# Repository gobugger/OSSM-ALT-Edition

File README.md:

# OSSM ALT Edition
---
## 🎯 Overview

OSSM ALT Edition is a community-driven alternative version of the well-known [OSSM](https://github.com/KinkyMakers/OSSM-hardware) platform. A lot of time and effort has gone into this project. This has been possible thanks to all the previous work that has been done and several community members that helped test this. Do note that we are still in 'beta testing' phase and that you may run into issues. Please provide feedback to help improve the project. This project represents a ground-up redesign focused on:

- **Modern Power Delivery**: Custom 28V 140W USB-C PCB with comprehensive protection circuits
- **Simplified Assembly**: All-in-one clean design with easily sourceable components
- **European Sourcing**: BOM optimized for availability in Europe
- **Enhanced Performance**: Support for MGN12H and MGN15H rails with support for belts up to 15mm belt.
- **Open Source**: Fully open hardware

***Links***: KM [Discord community](https://kinkymakers.com) & [Ko-Fi](https://ko-fi.com/dododesigns) (for contributions / buying boards)

<sub>**Notice**: This version was developed without any involvement of the original OSSM / Research and Desire members. However, none of this would have been possible without their prior work which is greatly appreciated. Especially the work of [ArmpitMFG](https://github.com/armpitMFG) has been a great inspiration. </sub>

---

## ✨ Key Features

### Hardware Improvements
- **Custom 28V USB-C PCB** with extensive protection circuits
  - Over/under voltage protection
  - Reverse current protection
  - ESD protection on all exposed ports
  - Inrush current limiting
  - Hybrid polymer capacitors for stable power
  - Brake Chopper Add-On 360Watt
- **Dual Rail Options**
  - MGN15H for heavy-duty applications (up to 15mm belts)
  - MGN12H for lighter builds (up to 12mm belts)
- **Efficient Travel**: Rail length minus 150mm usable stroke
- **Compatible with Pitclamp Mini** and includes optimized alternative design with dowels

### Electronics & Firmware
- **ESP32-S3** microcontroller with integrated RS485 controller
- **WS2812 Status LED** (firmware support pending)
- **Made for [OSSM Rust](https://github.com/orange-gem/ossm-rs)** firmware
- Compatible with step/dir control for original firmware adaptation
- **Optional Brake Chopper PCB** for enhanced safety

### Design Philosophy
- Optimized for 3D printing (minimal supports required)
- Common, easily sourceable components
- Clean, simple assembly
- Comprehensive protection systems

---
  
## 📦 Bill of Materials

A comprehensive BOM with descriptions and links can be found [here](Assembly-Info/BOM-OSSM-ALT.csv). However, the parts below are a quick summary everything you need for building this complete version:

| **Part**           | **Description**                                             | **Costs** |
| -------------- | -------------------------------------------------------- | ----- |
| 57AIM30        | Motor                                                    | €110  |
| MGN15H Rail    | Rail 40cm                                                | €25   |
| Or MGN12H Rail    | Rail 40cm                                                | €21   |
| 625RS Bearing  | Belt Bearings                                            | €15   |
| M5 Bolts       | Complete kit                                             | €12   |
| M3 Bolts       | Complete kit                                             | €12   |
| Dowel Pins     | Precision pins                                           | €10    |
| GT2 Belt       | 50cm                                                     | €15   |
| GT2 20T pulley | 15mm                                                     | €10    | 
| Filament  | Max 500g | €20   |
| OSSM ALT 28V PCB   | Designs available for self-sourcing or buy through me to support this project. | €40   |
| **Total**      | Rough approximation. Check BOM for details.              | €270  |

📋 **[Complete BOM with part numbers and links](Assembly-Info/BOM-OSSM-ALT.csv)**

> **Note**: You will also need a remote control device. Compatible options include:
> - Official R&D remote
> - iOS/Android apps
> - Web control interface
> - M5 Remote (check firmware compatibility)

---

## 3D Printing Tips

500 grams of filament should be enough to complete the whole build including the main pitclamp (350 without). It is optimized as much as possible for 3D printing with only 1 part requiring a small amount of supports. The filament type should not matter for most standard build, but heavy users might want to rely on something sturdier like tough-PLA, PET-G, ASA or PC. The test builds have been printed with standard Bambulab basic PLA (Not matte/silk). 

**Filament Required**: ~500g for complete build including Pitclamp

**Recommended Materials**:
- **Standard Use**: PLA, PLA+
- **Heavy Use**: Tough-PLA, PETG, ASA, PC

**Important**: Follow the [detailed 3D printing guide](Assembly-Info/Print-Manual/README.md) carefully to ensure proper fit and function.

**Print Options**:
- Standard version (no branding)
- Multi-color branded version (AMS/toolchanger compatible)
- Single-color embossed version

---
## Assembly:

📺 **Video Assembly Guides**:
- [Part 1](https://youtu.be/EqzNXQzpHu0) 
- [Part 2](https://youtu.be/FnY4Sz64H2A) 

📖 **Written Assembly Guide**: In development

💬 **Need Help?** Join the KM [Discord community](https://kinkymakers.com) for assembly support and questions (Look for the OSSM ALT Project).

---

## 🔌 Main PCB Specifications

Most work has gone into this PCB. My vision for this Machine/PCB is that groups of people will self-source this PCB. From 10+ pieces this makes sense, so as long as you can find 10 people you should be able to buy this at an affordable price. The rest of the machine can be printed and uses off the shelf parts. I will also sell these boards for people that only need 1 PCB and want to help support this project (please not that a lot of my own money has gone into this and any support is greatly appreciated ([Ko-Fi](https://ko-fi.com/dododesigns))

### Technical Features

- **Power**: CH224Q for 28V USB-C PD 3.2 negotiation
- - Continuous 140Watt capable with 4 layer optimized PCB design (load tested)
- **Controller**: ESP32-S3 microcontroller with onboard antenna
- **Communication**: Integrated RS485 controller
- **Power Protection**:
  - Hybrid polymer capacitors
  - Inrush current limiting
  - Over/under voltage protection
  - Reverse current protection
- **Additional Features**:
  - Dedicated USB-C debugging port
  - ESD protection on all exposed ports
  - WS2812 status LED
  - Brake chopper expansion support

**Design Tool**: KiCAD 9  
**Manufacturing**: Optimized for major PCB fabrication houses

### Optional Brake Chopper Add-on

Enhanced protection for heavy-duty use:
- **Dissipation**: 12W continuous, 360W short-term spikes
- **Protection Threshold**: 33V (protects 36V TVS diode)
- **Purpose**: Back-EMF spike suppression
- **Recommended For**: Heavy users and added safety margin

This was mainly a fun side project for me which also adds functionality. It is basically an improved version of a Pololu Shunt Regulator, but completely redesigned with an on-board gate driver, 12V LDO, and 12watts of power resistors (2 sides assembly up to 24watt). This PCB was designed to be very cheap and easy to produce. 

---
## 🔋 Compatible Power Sources

This design is focused around PD, so it only makes sense to provide some options that are tested.

> **Important**: Use a USB-C cable with E-marker chip for >3A current. Standard cables will limit performance.

### Tested & Confirmed

| Device | Type | Rating | Status | Recommended | Rating | Notes |
|--------|------|--------|--------|-------|------|-----|
| [Apple 140W USB-C Adapter](https://www.apple.com/nl/shop/product/mw2m3zm/a/usb%E2%80%91c-lichtnetadapter-van-140-w) | Wall Adapter | 28V / 5A (140W) | 🔬 Tested | ✅ Recommended| ★★★★★ (5)| Excellent reliability and quality, Only ~€60 (will likely not work with other pcb's besides the OSSM ALT since it requires inrush current protection) |
| [Ugreen 200W Powerbank](https://eu.ugreen.com/products/ugreen-nexode-power-bank-200w-25000mah) | Powerbank | 28V / 5A (140W) | 🔬 Tested| ✅ Recommended|★★★★★ (5)| Great portable option that negotiates with almost any chip. Best power bank I have tested.|
| [Anker 140W Wall Adapter](https://www.anker.com/products/a2697-anker-charger-140w-4-port) | Wall Adapter | 28V / 5A (140W) | 🔬 Tested| ✅ Recommended|★★★★☆ (4)| Works well, but you will definitely feel it get hot at prolonged 140W and after 20 minutes or so it will lower the power to cool down. 100Watts continuous is fine so for the gold motor there are no problems. I have yet to see a supported motor that pulls 140W continuous. 
| [Sitecom 140W Wall adapter](https://www.action.com/nl-nl/p/3221194/sitecom-usb-wandoplader/) | Wall Adapter | 28V / 5A (140W)|🔬 Tested | ✅ Recommended| ★★★★☆ (4) | Cheapest adapter of the list (~€20). Did not do any extensive testing yet, but it negotiates 28V and 20V fine. I was also able to load test it at 140W and you can feel it get warmer similar to the Anker one, but it seems to hold up fine. At it's price point it is probably a very good deal (even comes with a cable), but we don't know if it's easy to source since right now it's sold at 'action' which normally changes its inventory quite quickly. 
| [Ugreen 100W Wall Adapter](https://www.amazon.nl/dp/B091TV6LWN) | Wall Adapter | 20V / 5A (100W) | 🔬 Tested | ⚠️ Lower Power|★★★☆☆ (3) |Works okay, but do notice that this one does not support 28V. If you have the OSSM-Alt pcb at 28V and still try to power it, it will work but negotiates down to 20V. |
| [Framework 180W Adapter](https://frame.work/nl/en/products/16-power-adapter?v=FRANCR000F) | Wall Adapter | 36V / 5A (180W) | 🔬 Tested | ⚠️ Lower Power | ★★★☆☆ (3) | Quality wise I believe this is a good adapter, but it has a lot of difficulty negotiating with several common cheap PD chips. So it won't negotiate above 20V on the OSSM-ALT PCB and it also does not seem to support I2C with this chip either. Therefore, not really recommended unless you already have it and just power a motor at max 100W. 
| Apple 67W Adapter | Powerbank | 20V / 3.3A (67W) | 🔬 Tested | ⚠️ Lower Power | ★★☆☆☆ (2.5) | Negotiates well and also supports I2C negotiation. 67W is however on the lower side, so this is definitely not recommended for heavy usage. Still, this was the adapter I first tested my OSSM with and from my experience 67W is enough for most light play.  |
| Xiaomi Mi 50W | Powerbank | 20V / 2A (40W) | 🔬 Tested | ⚠️ Low Power | ★★☆☆☆ (2) | Not recommended. Negotiates well, but low power. Still for a very light weight OSSM it might. be fine.  |

**Have you tested another power source?** Please share your results!

---

## ❤️ Support the Project

If you've built an OSSM ALT and want to support continued development:

### Financial Support

- **PCB Purchase**: Buy boards from me to support the project (Discord PM, Ko-Fi (soon))
- **Buy a hardware kit**: If there is enough demand, I might start selling some hardware kits 
- **Donations**: [Ko-Fi](https://ko-fi.com/dododesigns) *(or contact me on Discord)*

### Non-Financial Support

- ⭐ **Star this repository** to increase visibility
- 📢 **Share the project** with your community
- 📸 **Share your build** with photos and feedback on Discord
- 📖 **Contribute documentation** and improvements

---

## 📜 License

This project is **Open Source Hardware**.

All hardware design files (including PCB schematics, layouts, and 3D mechanical design files) are licensed under the **CERN Open Hardware Licence Version 2 – Strongly Reciprocal (CERN-OHL-S-2.0)**.

You are free to:
- Use, study, modify, and manufacture this design

Under the following conditions:
- **Attribution** must be given to the original author(s)
- **All modified versions and derivatives must be released under the same license**
- **Complete corresponding source files must be made available**

---

## 🙏 Acknowledgments

Special thanks to:

### Core Contributors
- **OrangeMurker & Nakata** - OSSM Rust firmware development and invaluable feedback
- **Beta Testers** - All community members who tested and provided feedback

### Inspiration & Prior Art
- **[armpitMFG](https://github.com/armpitMFG)** - Front/end effector designs and Pitclamp Mini
- **Original OSSM / R&D Team** - Foundation and inspiration for this project

### Community
- All contributors who have improved this design
- Discord community members providing support and feedback

---

## ⚠️ Disclaimer

This project is currently in **beta testing phase**. While extensively tested, you may encounter issues. Please provide feedback to help improve the project.

**Safety**: This is a DIY project involving motors and electronics. Build and use at your own risk. Ensure all safety precautions are followed during assembly and operation.

---

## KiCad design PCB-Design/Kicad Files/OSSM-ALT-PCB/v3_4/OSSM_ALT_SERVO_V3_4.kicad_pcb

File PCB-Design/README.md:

# PCB Design

This folder contains everything related to the two PCBs of the OSSM ALT Edition (the main PCB and the brake chopper), organized as follows:

| Folder | Contents |
| ------ | -------- |
| [Schematic and Design](Schematic%20and%20Design/) | The schematics of both PCBs and their STEP files |
| [Production Files](Production%20Files/) | A manual on ordering, plus all the files needed to produce the PCBs yourself (Gerbers, BOM, CPL) |
| [Kicad Files](Kicad%20Files/) | The KiCad project files, if you wish to edit things |

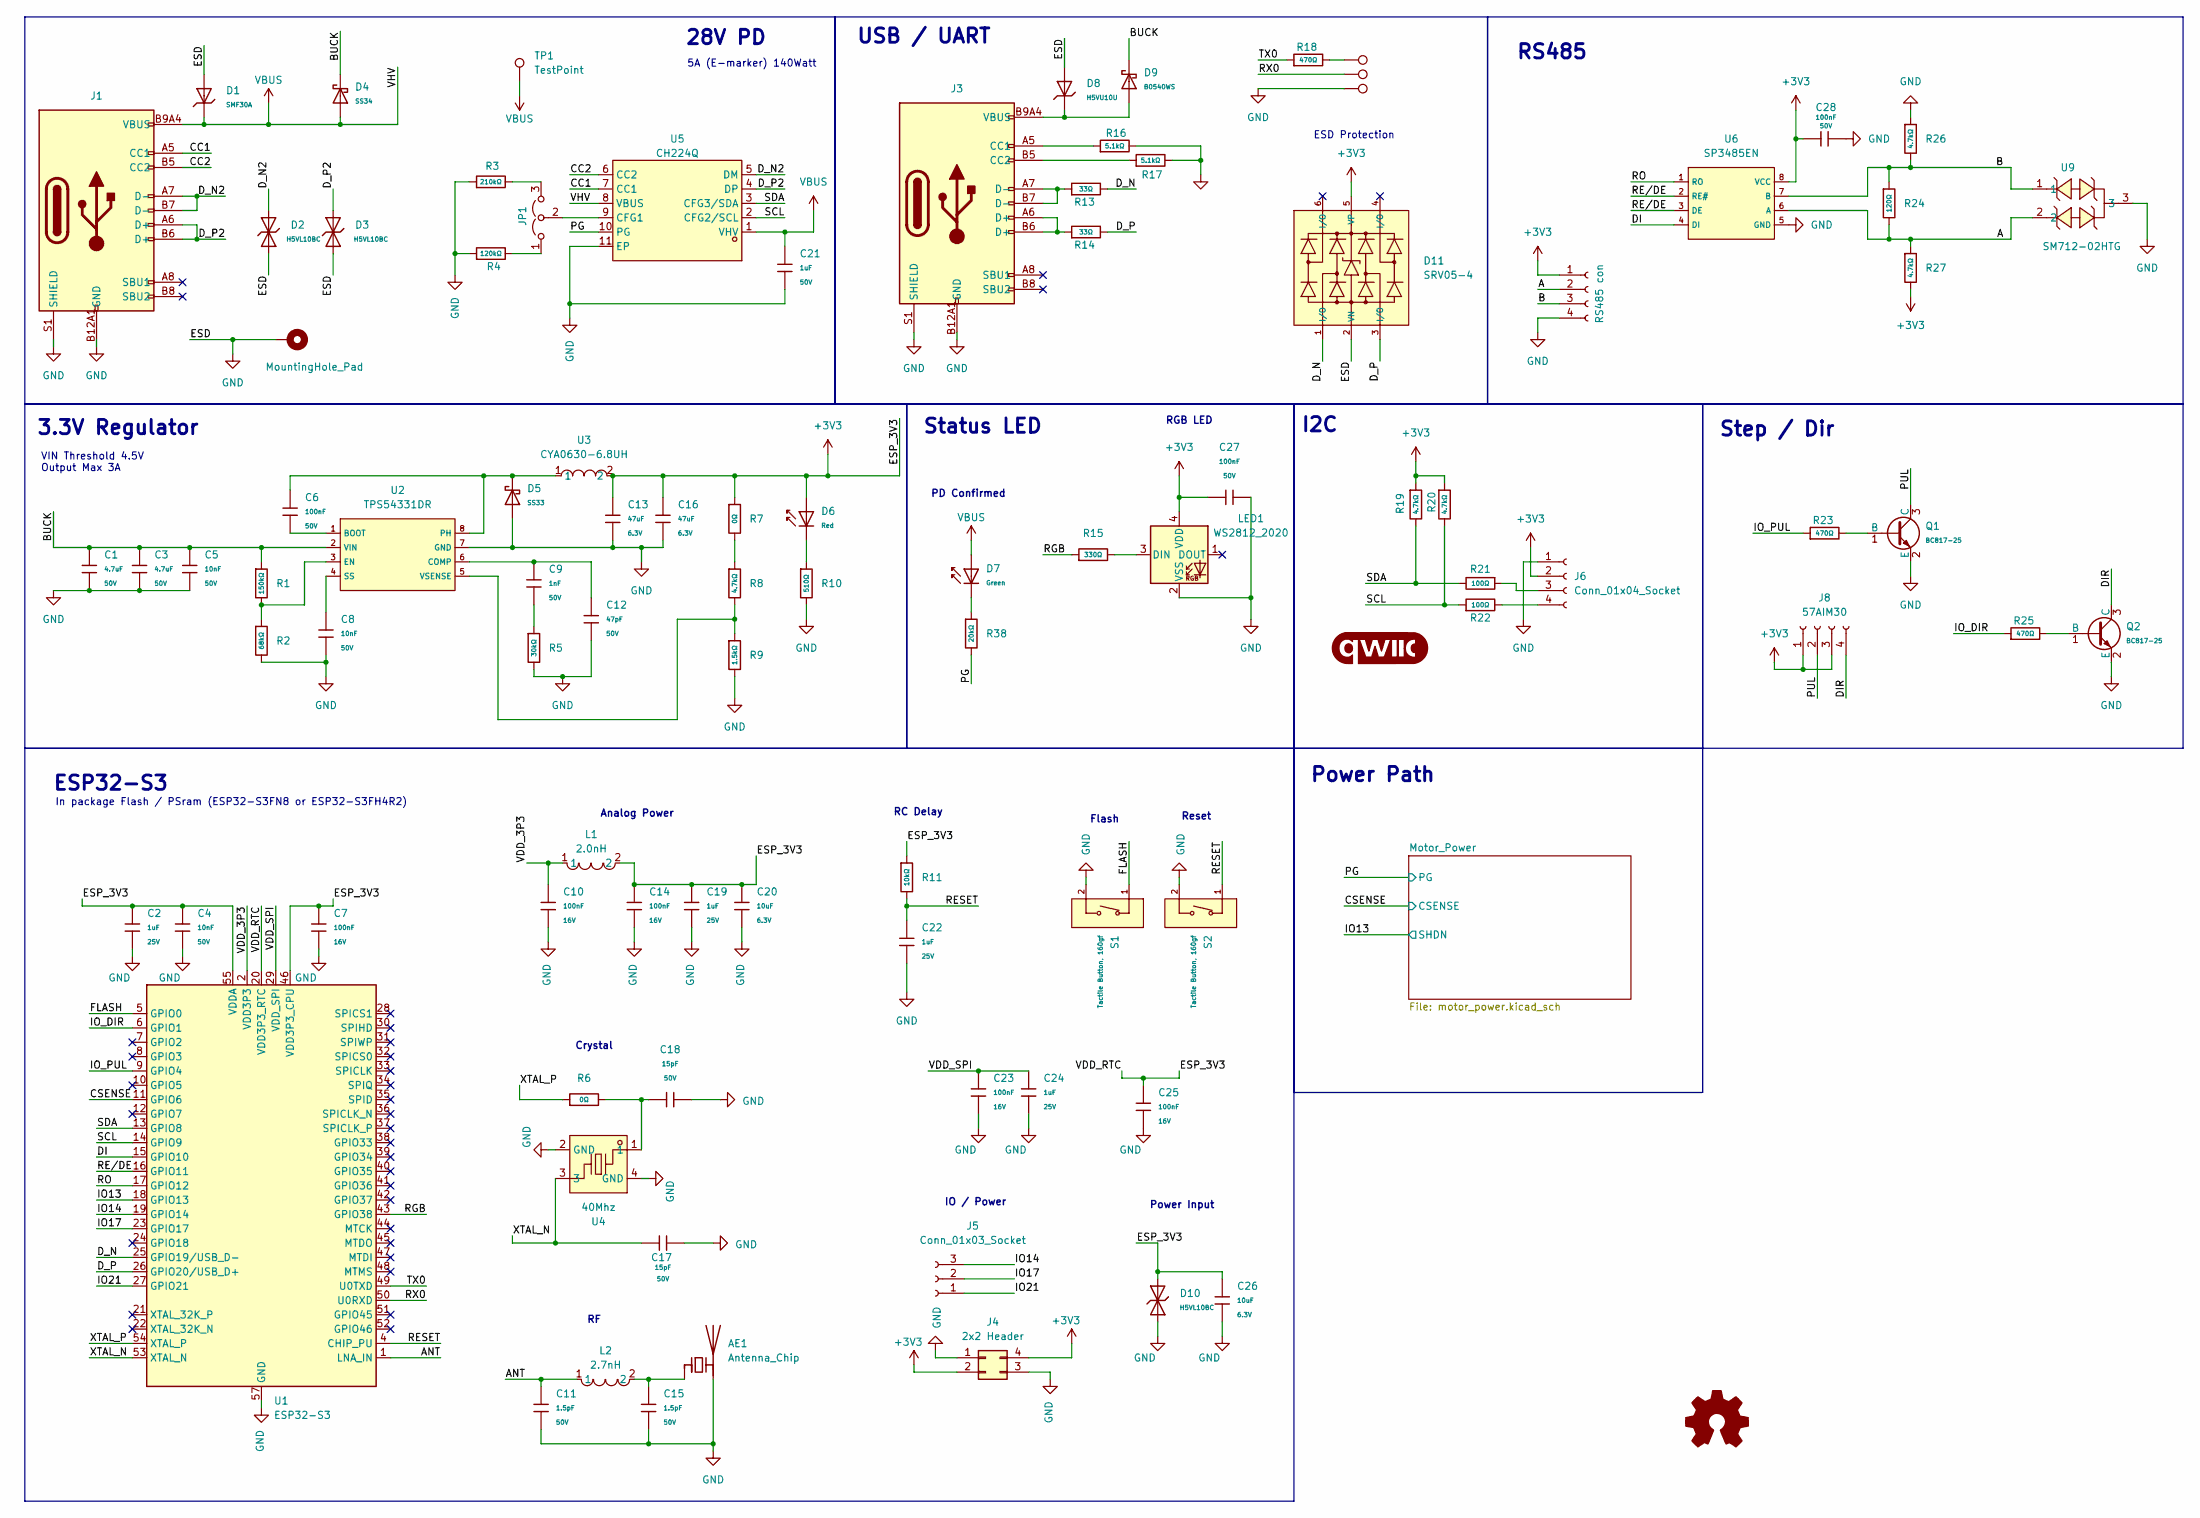
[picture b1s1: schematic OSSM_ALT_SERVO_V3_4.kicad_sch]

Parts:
AE1: Antenna_Chip; Texas_SWRA117D_2.4GHz_Left
C1, C3: 4.7uF; C_1206; Voltage Rated 50V; Tolerance ±10%; Part 1206B475K500NT; LCSC C29823
C2, C19, C22, C24: 1uF; C_0402; Voltage Rated 25V; Tolerance ±10%; Part CL05A105KA5NQNC; LCSC C52923
C4, C5, C8: 10nF; C_0402; Voltage Rated 50V; Tolerance ±10%; Part CL05B103KB5NNNC; LCSC C15195
C6, C27, C28: 100nF; C_0402; Voltage Rated 50V; Tolerance ±10%; Part CL05B104KB54PNC; LCSC C307331
C7, C10, C14, C23, C25: 100nF; C_0402; Voltage Rated 16V; Tolerance ±10%; Part CL05B104KO5NNNC; LCSC C1525
C9: 1nF; C_0402; Voltage Rated 50V; Tolerance ±10%; Part 0402B102K500NT; LCSC C1523
C11, C15: 1.5pF; C_0402; Voltage Rated 50V; Part 0402CG1R5C500NT; LCSC C1552
C12: 47pF; C_0402; Voltage Rated 50V; Tolerance ±5%; Part 0402CG470J500NT; LCSC C1567
C13, C16: 47uF; C_0805; Voltage Rated 6.3V; Tolerance ±20%; Part CL21A476MQYNNNE; LCSC C16780
C17, C18: 15pF; C_0402; Voltage Rated 50V; Tolerance ±5%; Part 0402CG150J500NT; LCSC C1548
C20, C26: 10uF; C_0402; Voltage Rated 6.3V; Tolerance ±20%; Part CL05A106MQ5NUNC; LCSC C15525
C21: 1uF; C_0603; Voltage Rated 50V; Tolerance ±10%; Part CL10A105KB8NNNC; LCSC C15849
D1: SMF30A; D_SOD-123FL; Breakdown Voltage 33.3V; Part SMF30A; LCSC C19077518
D2, D3, D10: H5VL10BC; D_DFN1006-2L; Part H5VL10BC; LCSC C20615784
D4: SS34; D_SMA; Forward Voltage (Vf@If) 550mV@3A; Reverse Voltage (Vr) 40V; Part SS34; LCSC C8678
D5: SS33; D_SMA; Part SS33; LCSC C28646294
D6: Red; D_0603; Part KT-0603R; LCSC C2286
D7: Green; D_0805; Part KT-0805G; LCSC C2297
D8: H5VU10U; D_DFN1006-2L; Breakdown Voltage 9V; Part H5VU10U; LCSC C22395519
D9: B0540WS; D_SOD-323; Part B0540WS; LCSC C7420326
D11: SRV05-4; SOT-23-6_L2.9-W1.6-P0.95-LS2.8-BL-1; Breakdown Voltage (Vbr) 6V; Clamping Voltage@Ipp 12.5V; Part SRV05-4; LCSC C7420376
G1: qwiic_Logo; qwiic_3mm
H1: MountingHole_Pad; MountingHole_3.2mm_M3_Pad
J1, J3: Connector, USB-TYPE-C-16P; TYPE-C-SMD_HX-TYPE-C-16PIN; LCSC C2927039
J4: 2x2 Header; PinHeader_2x02_P2.54mm_Vertical
J5: Conn_01x03_Socket; PinHeader_1x03_P2.54mm_Vertical
J6: Conn_01x04_Socket; JST_SH_SM04B-SRSS-TB_1x04-1MP_P1.00mm_Horizontal; LCSC C51940130
J7: RS485 con; OSSM ALT RS485 Connector
J8: 57AIM30; JST_PH_B4B-PH-K_1x04_P2.00mm_Vertical
JP1: Jumper_3_Open; PinHeader_1x03_P2.54mm_Vertical
L1: 2.0nH; L0402; LCSC Part C18216
L2: 2.7nH; L0402; LCSC C778766
LED1: WS2812_2020; LED_WS2812_2020; LCSC C42417600
Q1, Q2: BC817-25; Q_SOT-23; Part BC817-25; LCSC C20069154
R1: 150kΩ; R_0402; Overload Voltage (Max) 75V; Tolerance ±1%; Part 0603WAF1503T5E; LCSC C25755
R2: 68kΩ; R_0402; Overload Voltage (Max) 75V; Tolerance ±1%; Part 0603WAF6802T5E; LCSC C36871
R3: 210kΩ; R_0603; Overload Voltage (Max) 75V; Tolerance ±1%; Part 0603WAF2203T5E; LCSC C22952
R4: 120kΩ; R_0603; Overload Voltage (Max) 75V; Tolerance ±1%; Part 0603WAF1203T5E; LCSC C25808
R5: 30kΩ; R_0402; Overload Voltage (Max) 75V; Tolerance ±1%; Part 0603WAF3002T5E; LCSC C25553
R6, R7: 0Ω; R_0402; Overload Voltage (Max) 50V; Tolerance ±1%; Part 0402WGF0000TCE; LCSC C17168
R8, R19, R20, R26, R27: 4.7kΩ; R_0402; Overload Voltage (Max) 50V; Tolerance ±1%; Part 0402WGF4701TCE; LCSC C25900
R9: 1.5kΩ; R_0402; Overload Voltage (Max) 50V; Tolerance ±1%; Part 0402WGF1501TCE; LCSC C25867
R10: 510Ω; R_0603; Overload Voltage (Max) 75V; Tolerance ±1%; Part 0603WAF5100T5E; LCSC C23193
R11: 10kΩ; R_0402; Overload Voltage (Max) 50V; Tolerance ±1%; Part 0402WGF1002TCE; LCSC C25744
R13, R14: 33Ω; R_0402; Overload Voltage (Max) 50V; Tolerance ±1%; Part 0402WGF330JTCE; LCSC C25105
R15: 330Ω; R_0402; Overload Voltage (Max) 50V; Tolerance ±1%; Part 0402WGF3300TCE; LCSC C25104
R16, R17: 5.1kΩ; R_0402; Overload Voltage (Max) 50V; Tolerance ±1%; Part 0402WGF5101TCE; LCSC C25905
R18, R23, R25: 470Ω; R_0402; Overload Voltage (Max) 50V; Tolerance ±1%; Part 0402WGF4700TCE; LCSC C25117
R21, R22: 100Ω; R_0402; Overload Voltage (Max) 50V; Tolerance ±1%; Part 0402WGF1000TCE; LCSC C25076
R24: 120Ω; R_0603; Overload Voltage (Max) 75V; Tolerance ±1%; Part 0603WAF1200T5E; LCSC C22787
R38: 20kΩ; R_0603; Overload Voltage (Max) 75V; Tolerance ±1%; Part 0603WAF2002T5E; LCSC C4184
S1, S2: Tactile Button, 160gf; SW_TS-1088-AR02016; Voltage Rating (Dc) 12V; Part TS-1088-AR02016; LCSC C720477
TP1: TestPoint; TestPoint_Pad_D1.0mm
TP2, TP3, TP4: TestPoint; TestPoint_Pad_D1.5mm
U1: ESP32-S3; QFN-56-1EP_7x7mm_P0.4mm_EP4x4mm_ThermalVias; LCSC C2913196
U2: TPS54331DR; SOIC-8_L5.0-W4.0-P1.27-LS6.0-BL; Output Voltage 0.8V~25V; Input Voltage 3.5V~28V; Part TPS54331DR; LCSC C9865
U3: CYA0630-6.8UH; IND-SMD_L7.2-W6.6_GPSR0730; LCSC Part C5189749
U4: 40Mhz; ESP32 40Mhz Crystal C7206306; LCSC Part C7206306
U5: CH224Q; SON-10_L2.0-W2.0-P0.40-TL-EP; LCSC Part C46061833
U6: SP3485EN; SOIC-8_L5.0-W4.0-P1.27-LS6.0-BL; Supply Voltage 3.3V; Part SP3485EN-L/TR; LCSC C8963
U9: SM712-02HTG; SOT-23-3_L2.9-W1.3-P1.90-LS2.4-BR; LCSC Part C5449363

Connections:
+3V3: C2.1, C4.1, C7.2, C13.1, C14.1, C16.1, C19.1, C20.1, C25.2, C26.2, C27.2, C28.1, D6.2, D10.2, D11.5 (VP), J4.2, J4.4, J6.2, J7.1, J8.1, J8.3, L1.2, LED1.4 (VDD), R7.1, R11.1, R19.1, R20.1, R27.2, U1.20 (VDD3P3_RTC), U1.46 (VDD3P3_CPU), U1.55 (VDDA), U1.56 (VDDA), U3.2, U6.8 (VCC); also elsewhere on the board
/A: J7.2, R24.2, R27.1, U6.6 (A), U9.2
/ANT: C11.1, L2.1, U1.1 (LNA_IN)
/B: J7.3, R24.1, R26.2, U6.7 (B), U9.1
/BUCK: C1.1, C3.1, C5.1, D4.1, D9.1, R1.1, U2.2 (VIN)
/CC1: J1.A5 (CC1), U5.7 (CC1)
/CC2: J1.B5 (CC2), U5.6 (CC2)
/CSENSE: U1.11 (GPIO6); also elsewhere on the board
/DI: U1.15 (GPIO10), U6.4 (DI)
/DIR: J8.4, Q2.3 (C)
/D_N: D11.1 (I/O), R13.2, U1.25 (GPIO19/USB_D-)
/D_N2: D2.2, J1.A7 (D-), J1.B7 (D-), U5.5 (DM)
/D_P: D11.3 (I/O), R14.2, U1.26 (GPIO20/USB_D+)
/D_P2: D3.2, J1.A6 (D+), J1.B6 (D+), U5.4 (DP)
/FLASH: S1.1 (A), U1.5 (GPIO0)
/IO13: U1.18 (GPIO13); also elsewhere on the board
/IO14: J5.3, U1.19 (GPIO14)
/IO17: J5.2, U1.23 (GPIO17)
/IO21: J5.1, U1.27 (GPIO21)
/IO_DIR: R25.1, U1.6 (GPIO1)
/IO_PUL: R23.1, U1.9 (GPIO4)
/PG: R38.2, U5.10 (PG); also elsewhere on the board
/PUL: J8.2, Q1.3 (C)
/RESET: C22.1, R11.2, S2.1 (A), U1.4 (CHIP_PU)
/RE/DE: U1.16 (GPIO11), U6.2 (RE#), U6.3 (DE)
/RGB: R15.1, U1.43 (GPIO38)
/RO: U1.17 (GPIO12), U6.1 (RO)
/RX0: TP3.1 (1_1), U1.50 (U0RXD)
/SCL: R20.2, R22.1, U1.14 (GPIO9), U5.2 (CFG2/SCL)
/SDA: R19.2, R21.2, U1.13 (GPIO8), U5.3 (CFG3/SDA)
/TX0: R18.1, U1.49 (U0TXD)
/VDD_3P3: C10.1, L1.1, U1.2 (VDD3P3), U1.3 (VDD3P3)
/VDD_SPI: C23.1, C24.1, U1.29 (VDD_SPI)
/XTAL_N: C17.1, U1.53 (XTAL_N), U4.3
/XTAL_P: R6.1, U1.54 (XTAL_P)
GND: AE1.2 (PCB_Trace), C1.2, C2.2, C3.2, C4.2, C5.2, C7.1, C8.2, C10.2, C11.2, C12.2, C13.2, C14.2, C15.2, C16.2, C17.2, C18.2, C19.2, C20.2, C21.2, C22.2, C23.2, C24.2, C25.1, C26.1, C27.1, C28.2, D1.2, D2.1, D3.1, D5.2, D8.2, D10.1, D11.2 (VN), H1.1 (1_1), J1.A12B1 (GND), J1.B12A1 (GND), J1.S1 (SHIELD), J3.A12B1 (GND), J3.B12A1 (GND), J3.S1 (SHIELD), J4.1, J4.3, J6.1, J7.4, LED1.2 (VSS), Q1.2 (E), Q2.2 (E), R2.2, R3.1, R4.1, R5.2, R9.2, R10.2, R16.2, R17.2, R26.1, S1.2 (B), S2.2 (B), TP4.1 (1_1), U1.57 (GND), U2.7 (GND), U4.2 (GND), U4.4 (GND), U5.11 (EP), U6.5 (GND), U9.3; also elsewhere on the board
unnamed: AE1.1 (FEED), C15.1, L2.2
unnamed: C9.2, R5.1
unnamed: C18.1, R6.2, U4.1
unnamed: D6.1, R10.1
unnamed: D7.1, R38.1
unnamed: D8.1, D9.2, J3.A9B4 (VBUS), J3.B9A4 (VBUS)
unnamed: J3.A5 (CC1), R16.1
unnamed: J3.B5 (CC2), R17.1
unnamed: J3.A6 (D+), J3.B6 (D+), R14.1
unnamed: J3.A7 (D-), J3.B7 (D-), R13.1
unnamed: J6.3, R21.1
unnamed: J6.4, R22.2
unnamed: JP1.1 (A), R4.2
unnamed: JP1.3 (B), R3.2
unnamed: JP1.2 (C), U5.9 (CFG1)
unnamed: LED1.3 (DIN), R15.2
unnamed: Q1.1 (B), R23.2
unnamed: Q2.1 (B), R25.2
unnamed: R7.2, R8.1
unnamed: R18.2, TP2.1 (1_1)
unnamed: C6.2, U2.1 (BOOT)
unnamed: C9.1, C12.1, U2.6 (COMP)
unnamed: R1.2, R2.1, U2.3 (EN)
unnamed: C6.1, D5.1, U2.8 (PH), U3.1
unnamed: C8.1, U2.4 (SS)
unnamed: R8.2, R9.1, U2.5 (VSENSE)
VBUS: C21.1, D1.1, D4.2, D7.2, J1.A9B4 (VBUS), J1.B9A4 (VBUS), TP1.1 (1_1), U5.1 (VHV), U5.8 (VBUS); also elsewhere on the board

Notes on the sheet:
ESD Protection
IO / Power
In package Flash / PSram (ESP32-S3FN8 or ESP32-S3FH4R2)
Reset
Analog Power
RGB LED
5A (E-marker) 140Watt
Step / Dir
Status LED
PD Confirmed
28V PD
VIN Threshold 4.5V Output Max 3A
Power Path
RC Delay
USB / UART
3.3V Regulator
RS485
Flash
Power Input
Crystal
I2C
ESP32-S3

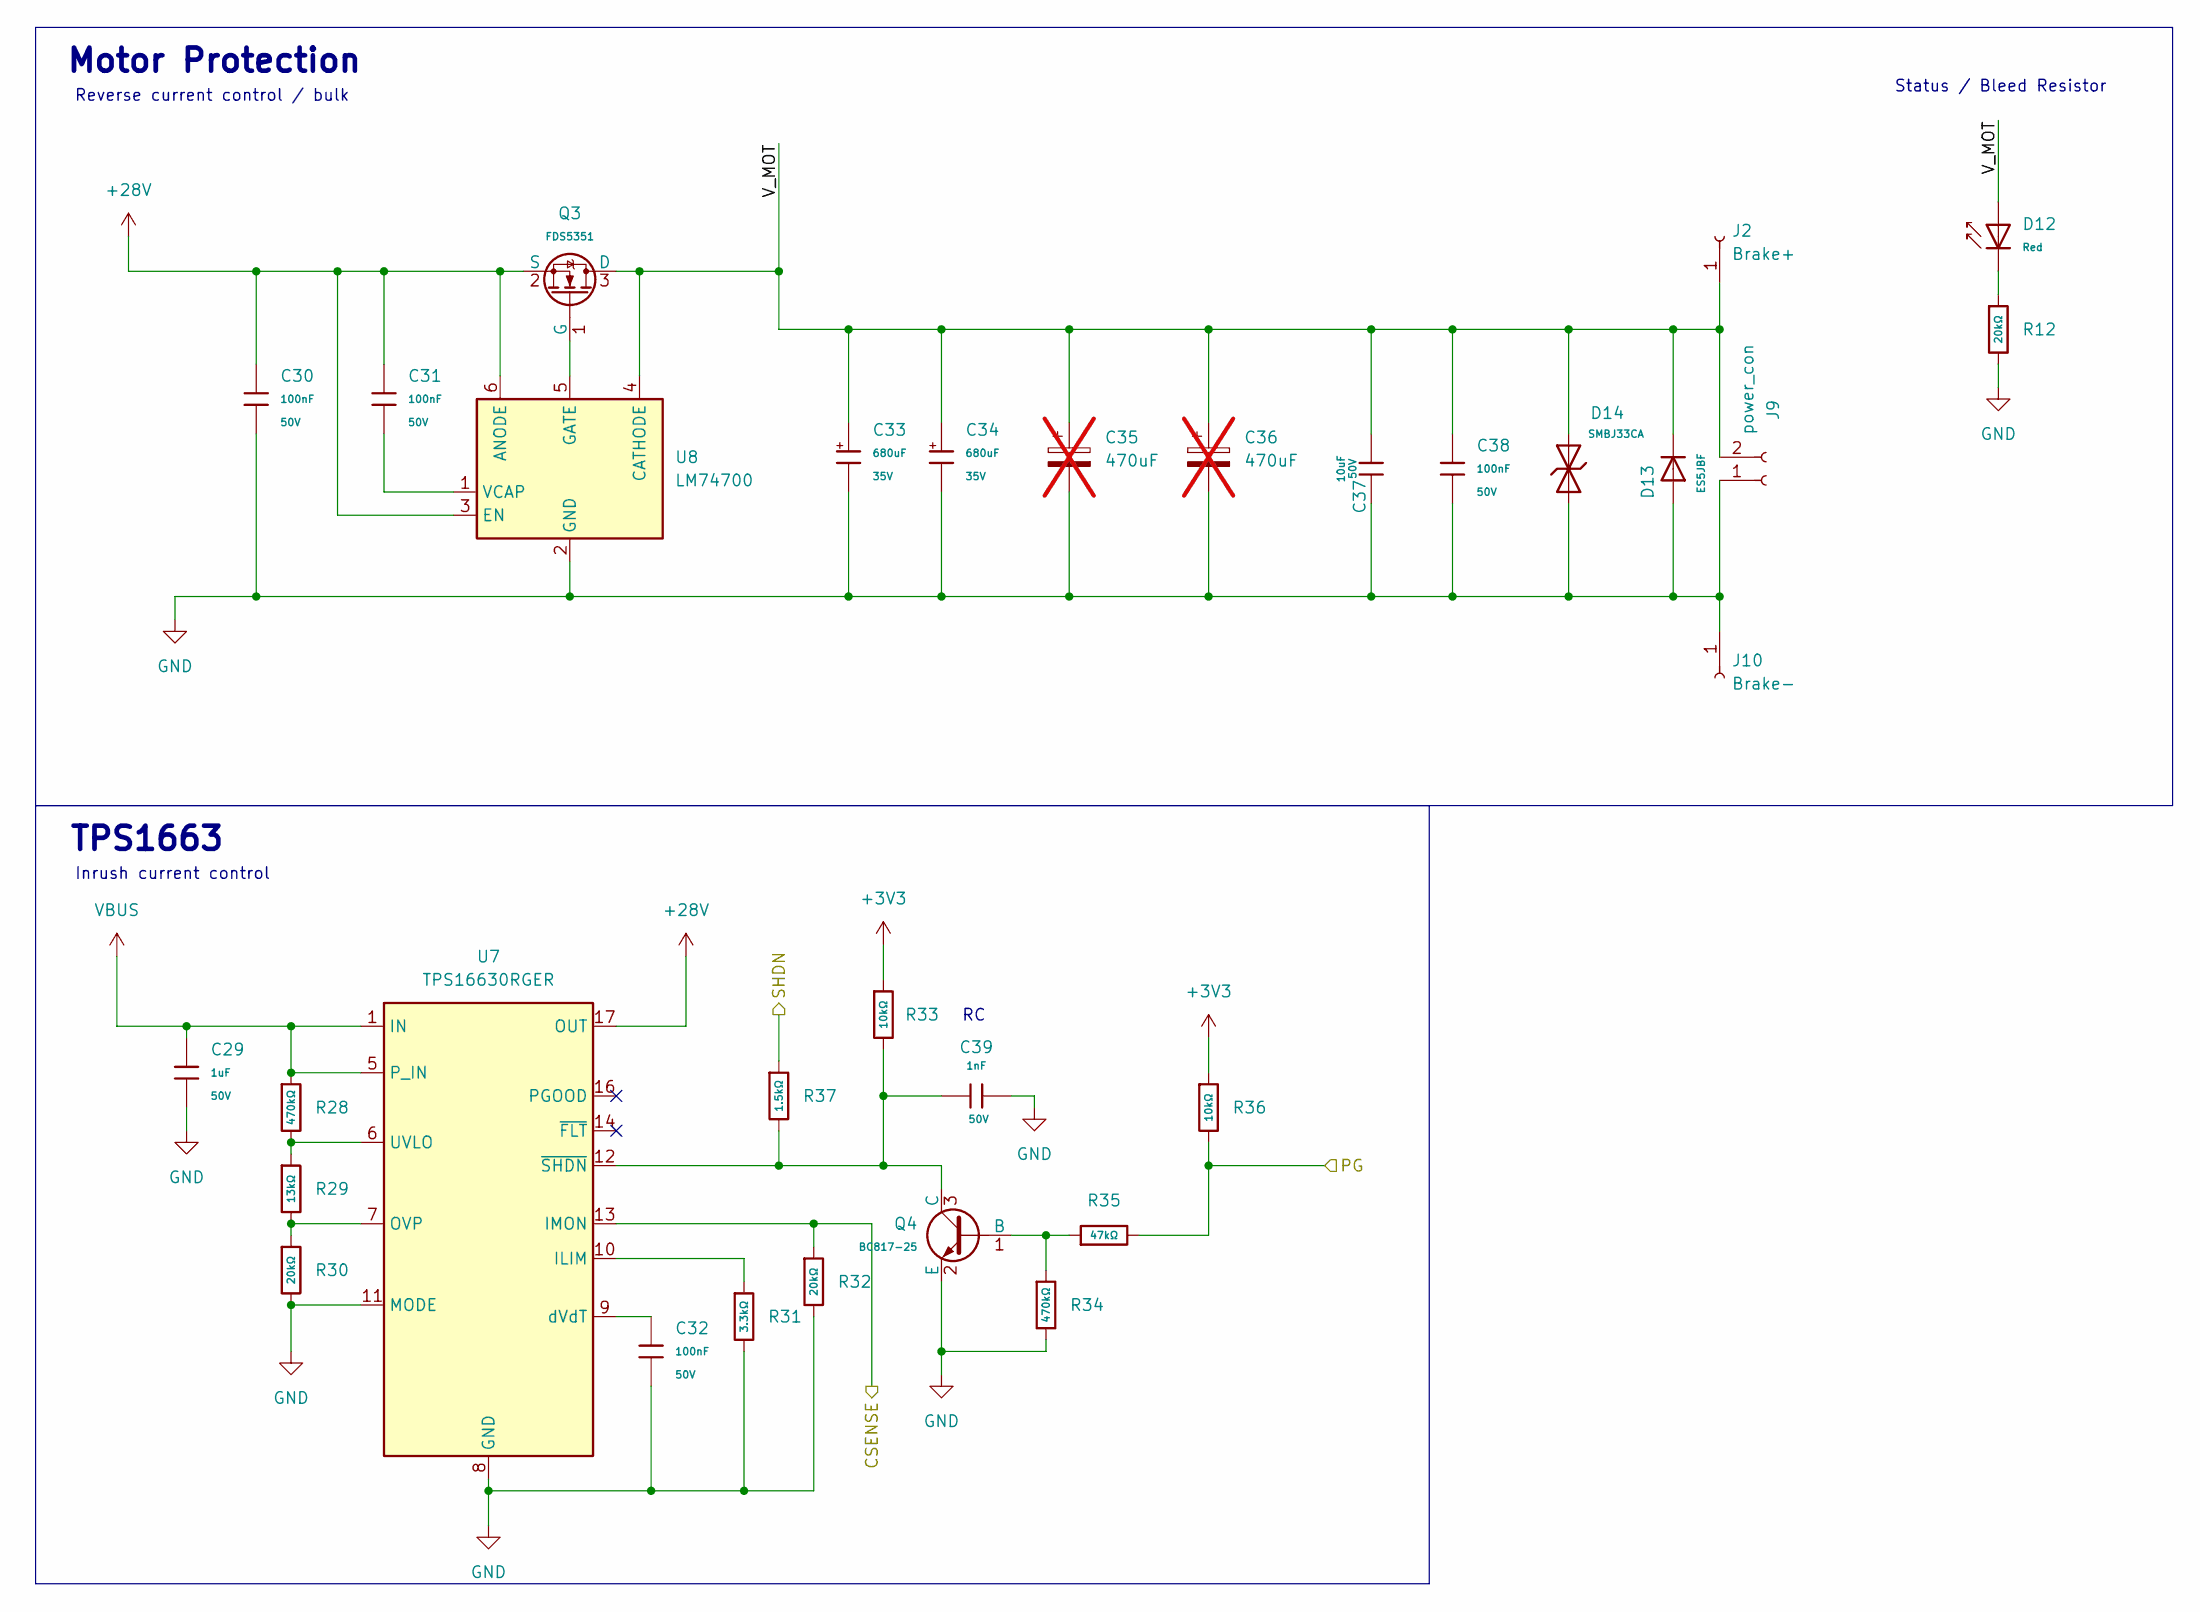
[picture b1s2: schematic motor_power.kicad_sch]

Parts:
C29: 1uF; C_0603; Voltage Rated 50V; Tolerance ±10%; Part CL10A105KB8NNNC; LCSC C15849
C30, C31, C32, C38: 100nF; C_0603; Voltage Rated 50V; Tolerance ±10%; Part CC0603KRX7R9BB104; LCSC C14663
C33, C34: 680uF; CAP-SMD_BD10.0-L10.3-W10.3-LS11.3-FD; Tolerance ±10%; Rated Voltage 35V; Part TAJA106K016RNJ; LCSC C46643177
C35, C36: 470uF; CP_Radial_D10.0mm_P5.00mm_P7.50mm; not fitted
C37: 10uF; C_1206; Voltage Rated 50V; Tolerance ±10%; Part CL31A106KBHNNNE; LCSC C13585
C39: 1nF; C_0402; Voltage Rated 50V; Tolerance ±10%; Part 0402B102K500NT; LCSC C1523
D12: Red; D_0603; Part KT-0603R; LCSC C2286
D13: ES5JBF; D_SMBF; Part ES5JBF; LCSC C18199154
D14: SMBJ33CA; D_SMB; Part SMBJ33CA; LCSC C19077587
J2: Brake+; SolderWirePad_1x01_SMD_3x6mm
J9: power_con; TerminalBlock_Phoenix_MKDS-1,5-2-5.08_1x02_P5.08mm_Horizont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
J10: Brake-; SolderWirePad_1x01_SMD_3x6mm
Q3: FDS5351; SO-8 N-channel mosfet FDS5351; Part 2N7002; LCSC C241809
Q4: BC817-25; Q_SOT-23; Part BC817-25; LCSC C20069154
R12, R30, R32: 20kΩ; R_0603; Overload Voltage (Max) 75V; Tolerance ±1%; Part 0603WAF2002T5E; LCSC C4184
R28, R34: 470kΩ; R_0603; Overload Voltage (Max) 75V; Tolerance ±1%; Part 0603WAF4703T5E; LCSC C23178
R29: 13kΩ; R_0603; Overload Voltage (Max) 75V; Tolerance ±1%; Part 0603WAF1302T5E; LCSC C22797
R31: 3.3kΩ; R_0603; Overload Voltage (Max) 75V; Tolerance ±1%; Part 0603WAF3301T5E; LCSC C22978
R33, R36: 10kΩ; R_0603; Overload Voltage (Max) 75V; Tolerance ±1%; Part 0603WAF1002T5E; LCSC C25804
R35: 47kΩ; R_0603; Overload Voltage (Max) 75V; Tolerance ±1%; Part 0603WAF4702T5E; LCSC C25819
R37: 1.5kΩ; R_0402; Overload Voltage (Max) 50V; Tolerance ±1%; Part 0402WGF1501TCE; LCSC C25867
U7: TPS16630RGER; VQFN-24-1EP_4x4mm_P0.5mm_EP2.5x2.5mm_ThermalVias; LCSC C1850279
U8: LM74700; SOT-23-6; LCSC C2941042

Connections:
+3V3: R33.1, R36.1; also elsewhere on the board
+28V: C30.1, C31.1, Q3.2 (S), U7.17 (OUT), U7.18 (OUT), U8.3 (EN), U8.6 (ANODE)
/CSENSE: R32.1, U7.13 (IMON); also elsewhere on the board
/IO13: R37.1; also elsewhere on the board
/Motor_Power/V_MOT: C33.1, C34.1, C35.1, C36.1, C37.1, C38.1, D12.2, D13.1, D14.2, J2.1 (Pin_1_1), J9.2, Q3.3 (D), U8.4 (CATHODE)
/PG: R35.2, R36.2; also elsewhere on the board
GND: C29.2, C30.2, C32.2, C33.2, C34.2, C35.2, C36.2, C37.2, C38.2, C39.2, D13.2, D14.1, J9.1, J10.1 (Pin_1_1), Q4.2 (E), R12.2, R30.2, R31.2, R32.2, R34.2, U7.8 (GND), U7.11 (MODE), U7.25 (GND), U8.2 (GND); also elsewhere on the board
unnamed: D12.1, R12.1
unnamed: Q3.1 (G), U8.5 (GATE)
unnamed: Q4.1 (B), R34.1, R35.1
unnamed: C39.1, Q4.3 (C), R33.2, R37.2, U7.12 (~SHDN)
unnamed: R31.1, U7.10 (ILIM)
unnamed: R29.2, R30.1, U7.7 (OVP)
unnamed: R28.2, R29.1, U7.6 (UVLO)
unnamed: C32.1, U7.9 (dVdT)
unnamed: C31.2, U8.1 (VCAP)
VBUS: C29.1, R28.1, U7.1 (IN), U7.2 (IN), U7.5 (P_IN); also elsewhere on the board

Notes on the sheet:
TPS1663
Reverse current control / bulk
Inrush current control
Motor Protection
Status / Bleed Resistor

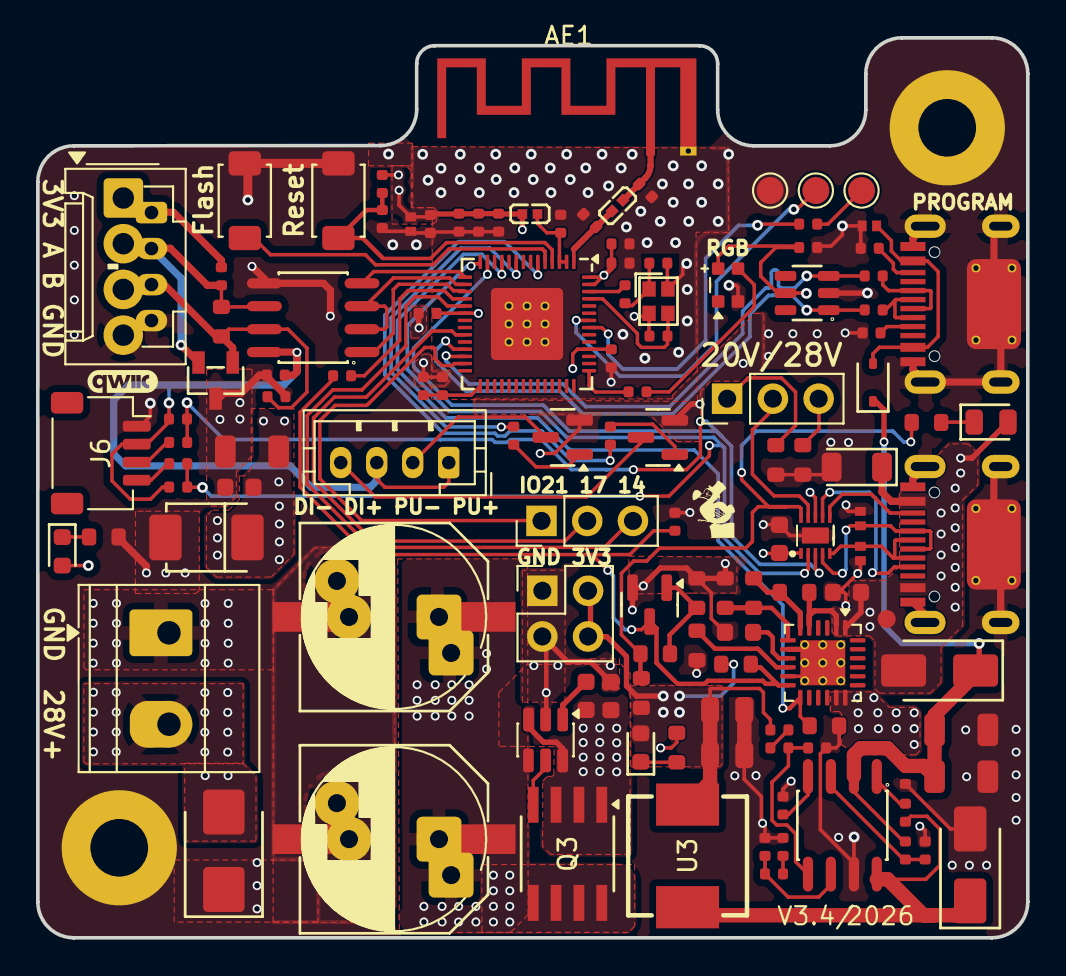
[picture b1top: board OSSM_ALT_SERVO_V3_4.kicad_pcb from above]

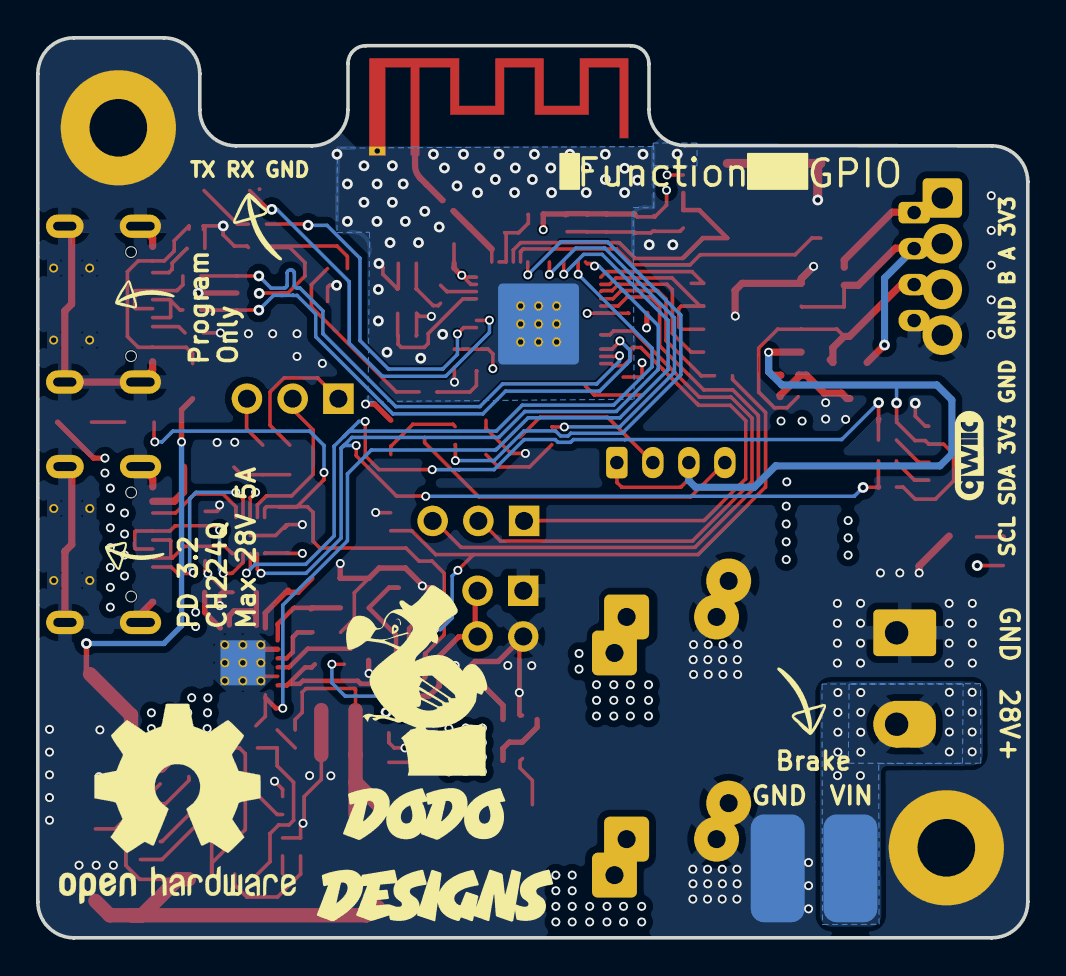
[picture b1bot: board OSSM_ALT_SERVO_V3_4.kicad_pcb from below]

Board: 4 copper layers, 55.0 x 50.0 mm, 128 parts (3 on the bottom side), 74 nets.

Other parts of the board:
MountingHole: (no value)
OSHWLOGO: OSHW-Logo2_14.6x12mm_SilkScreen

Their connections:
GND: MountingHole.1; also elsewhere on the board
